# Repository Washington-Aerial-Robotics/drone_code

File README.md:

# drone_code
WAAR Drone Code Base

Under IMU_ESP32_test_stuff, visual_task.py allows for attutide visualization, either using live data while connected to the ESP32, or simulating stored data. The box represents the imu itself, and the red line is the accel data.

To run visual_task.py using simulated data, just ensure you have the python packages under requirements.txt, and enter "S" when prompted.

To run visual_task.py using live data, first connect to the esp32 and update PORT under visual_task.py and platformio.ini. Ensure all packages under requirements.txt are installed, then simply run visual_task.py and enter "C" when prompted.

TODO:

In general, start making objects instead of making big scripts.

Ensure proper madgewick filtering. Change visualization to use quaternions from madgewick filter. Optimize refresh rates. Add option to print out script suitable for the magneto calibration tool.

Design simple kalman filter for position. Create alternate visualizer which tracks position as well as attiude. Consider adding offset parameters for how far the imu is away from the cg of the drone.

Object for visualization, simple rotations, and for general positioning, both using quaternions.

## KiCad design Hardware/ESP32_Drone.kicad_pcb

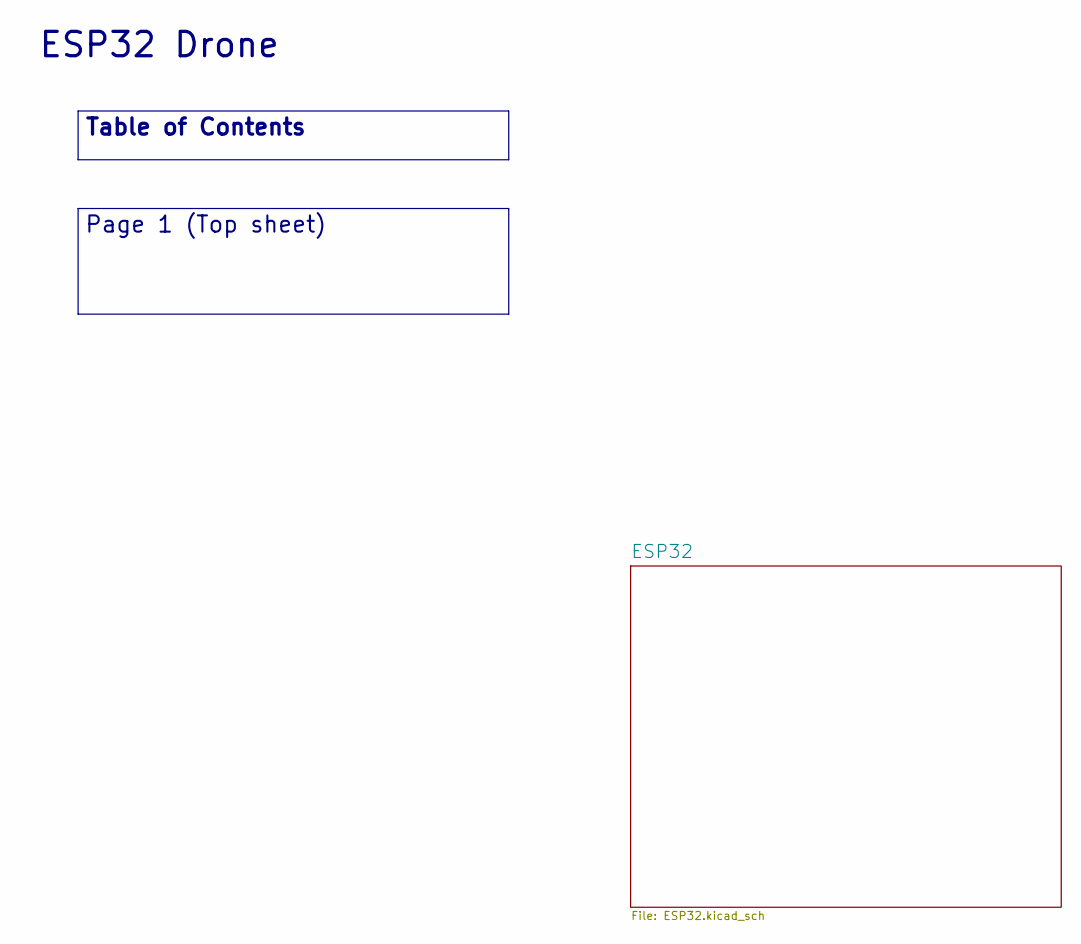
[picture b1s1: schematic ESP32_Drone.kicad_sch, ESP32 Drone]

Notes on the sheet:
ESP32 Drone
Table of Contents
Page 1 (Top sheet)

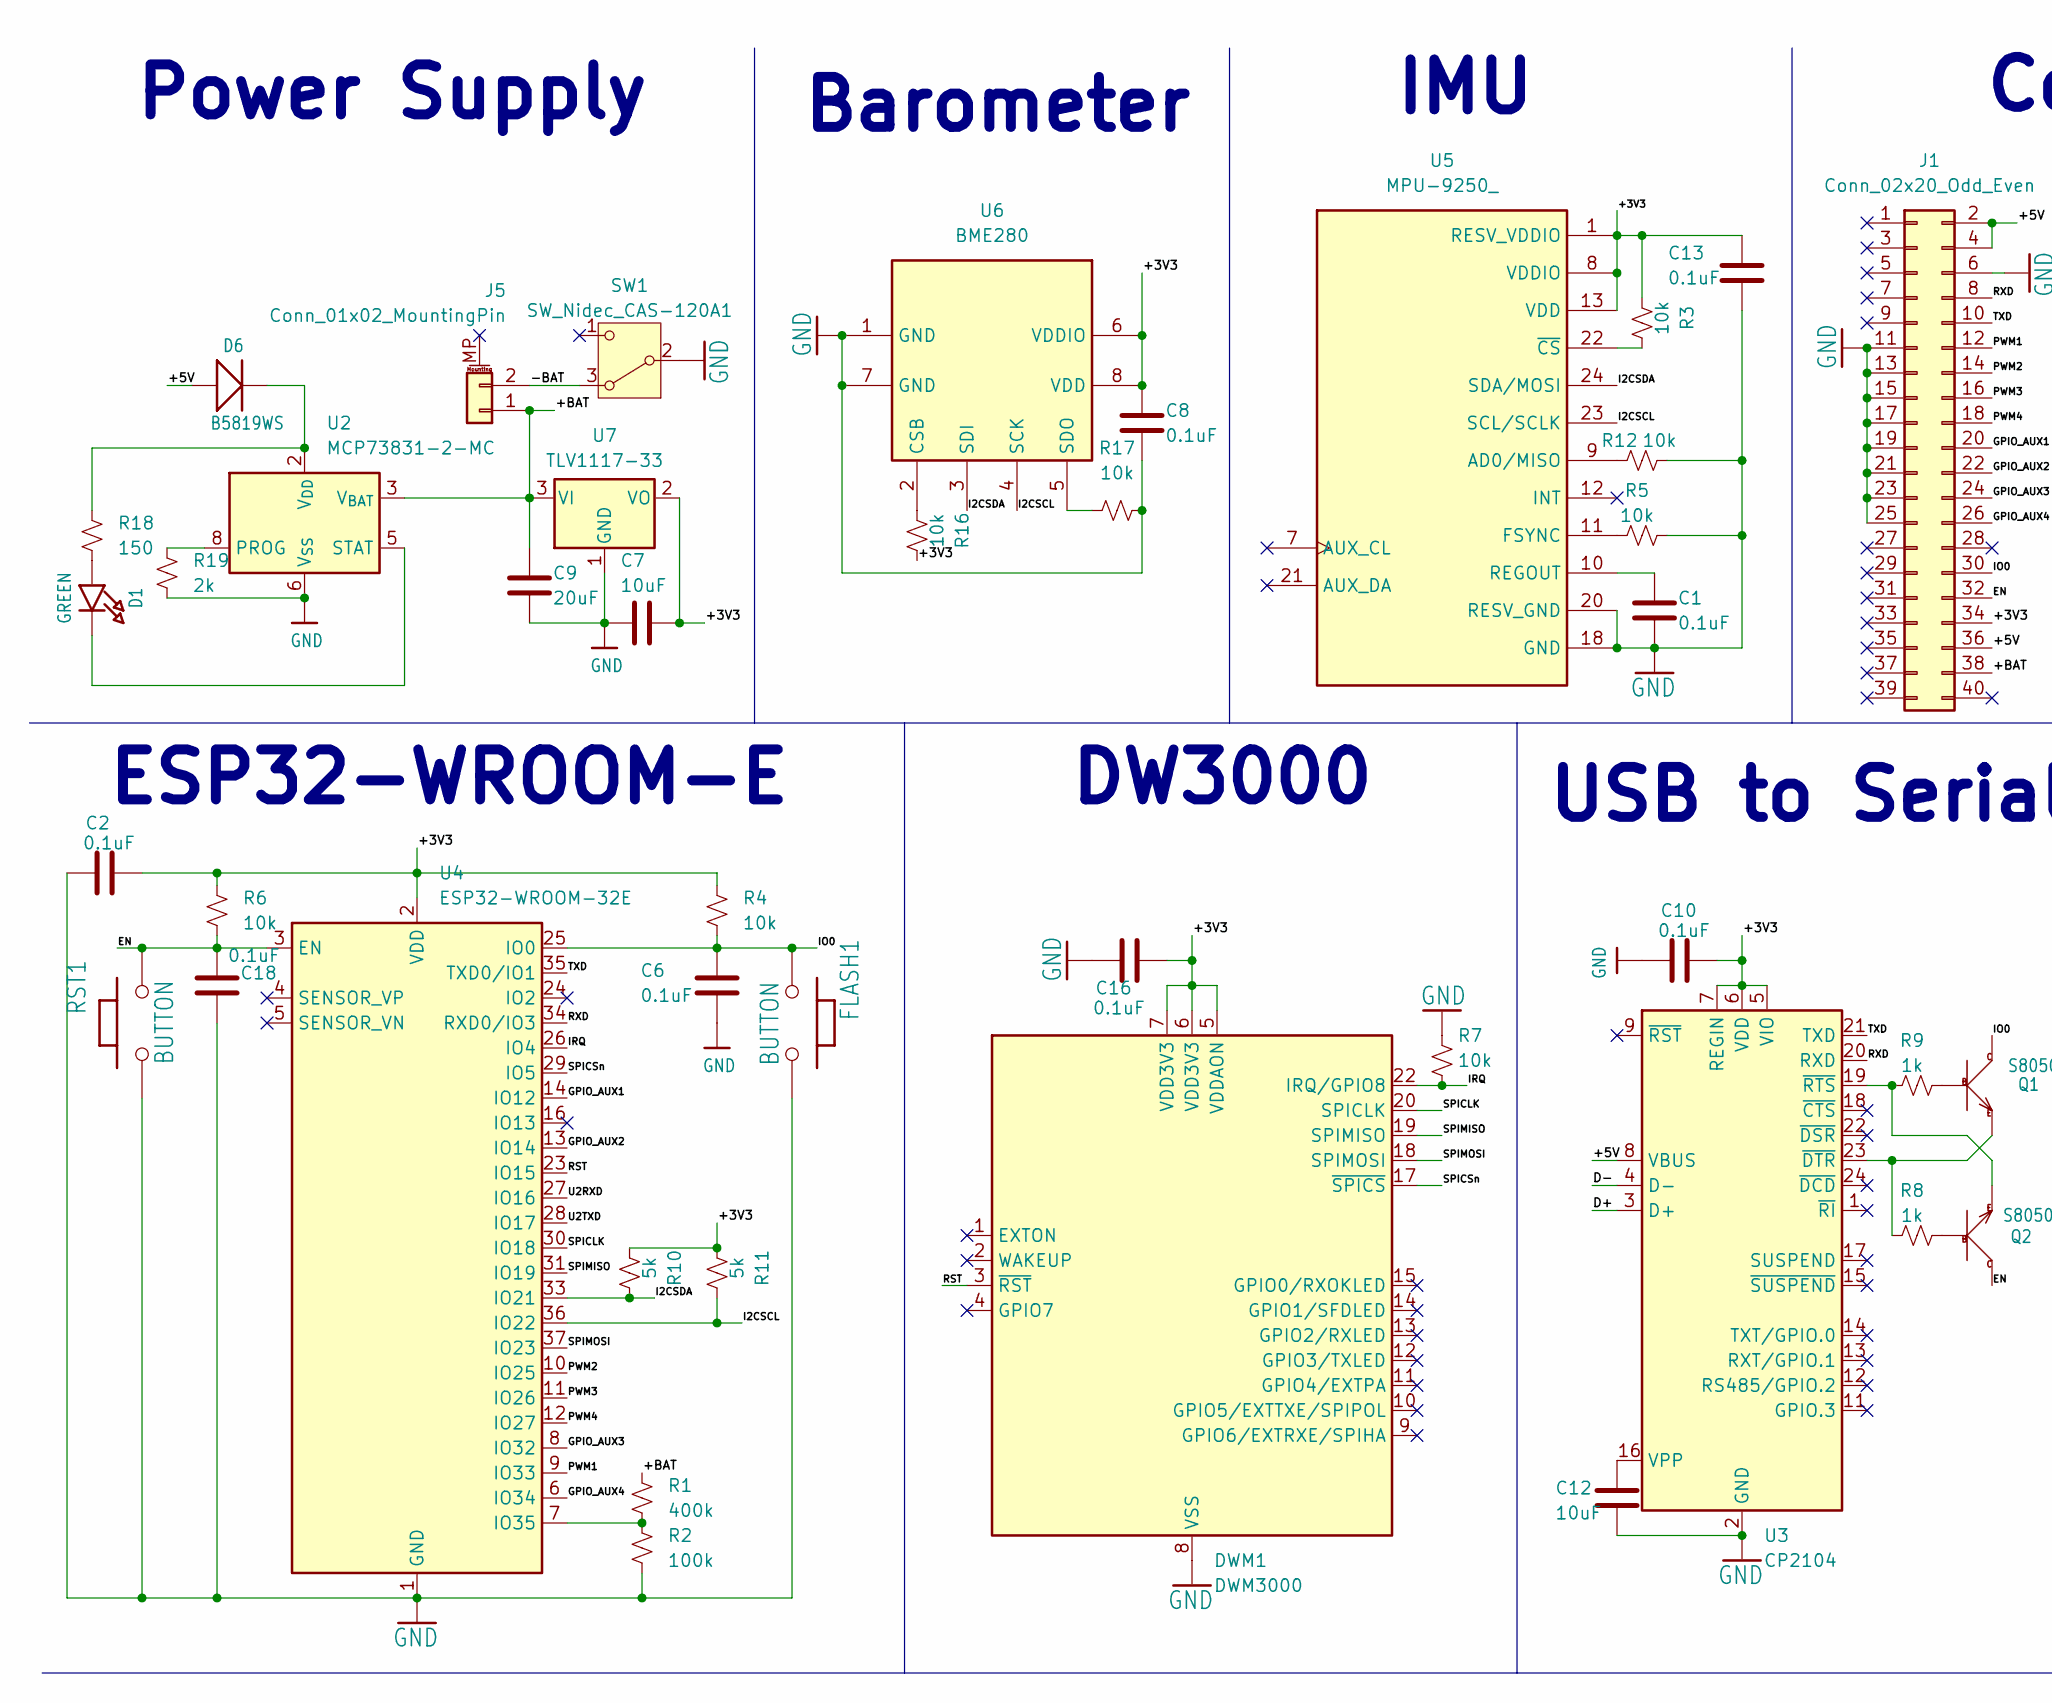
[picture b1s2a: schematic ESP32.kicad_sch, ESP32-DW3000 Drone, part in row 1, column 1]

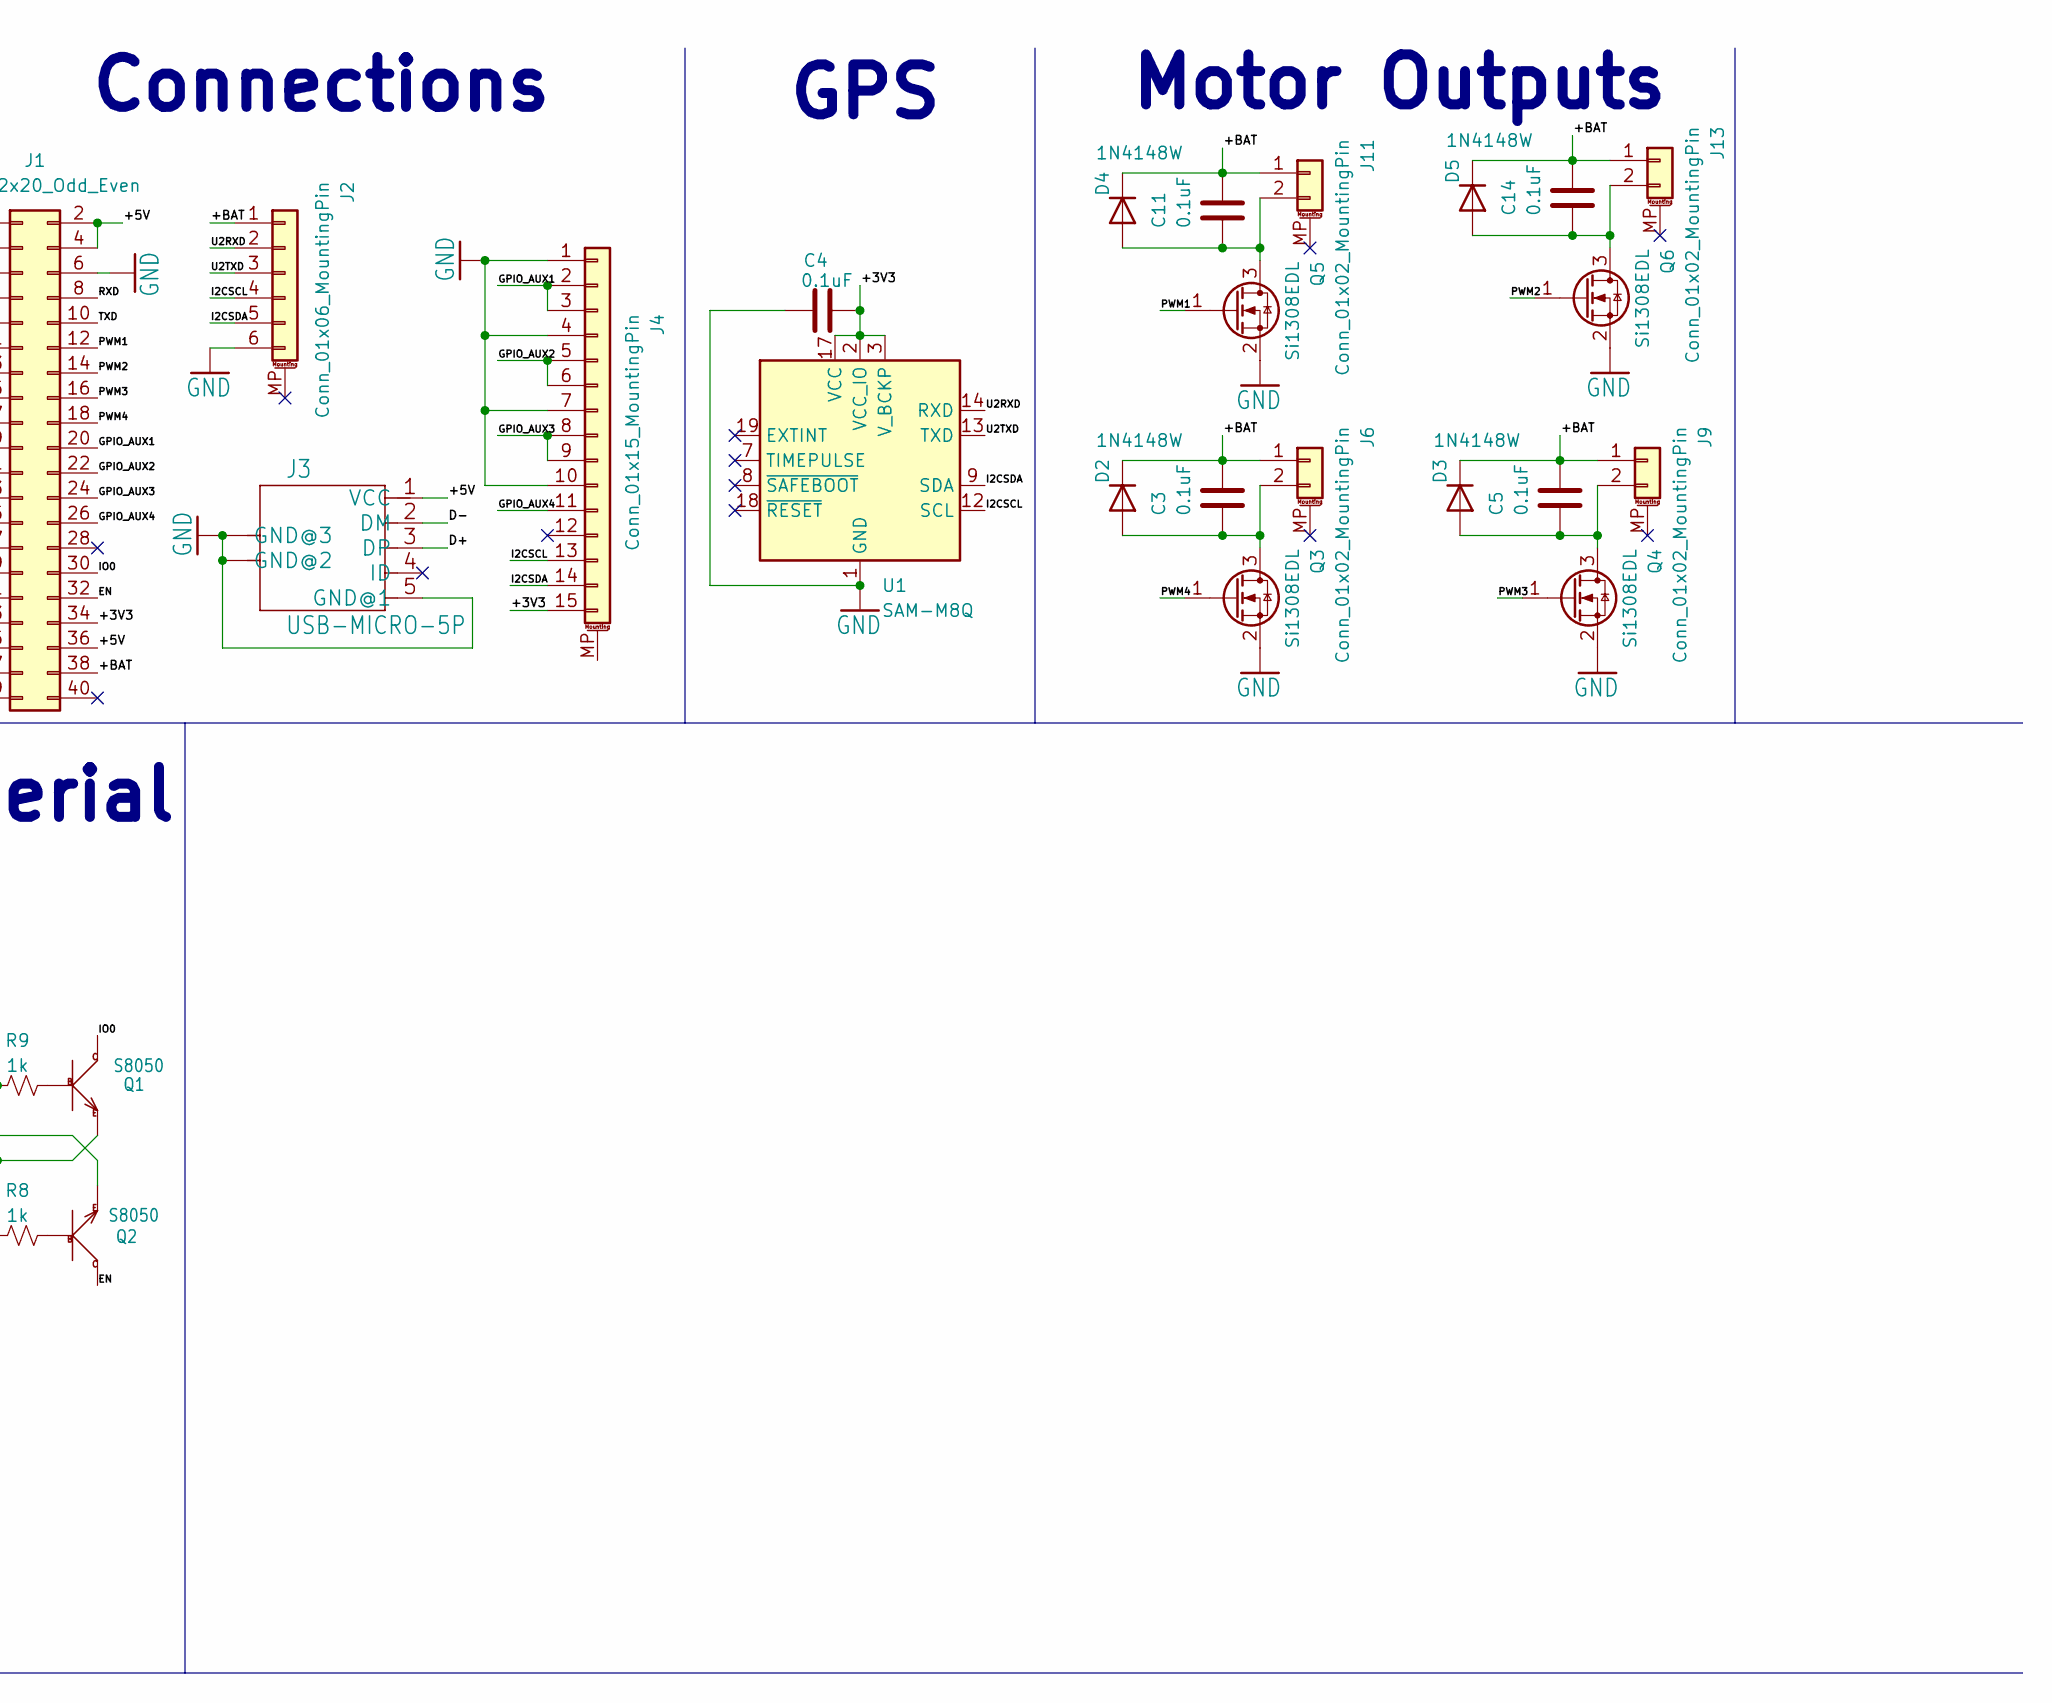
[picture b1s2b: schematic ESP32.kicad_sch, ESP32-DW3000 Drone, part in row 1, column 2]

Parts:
C1, C2, C3, C4, C5, C6, C8, C10, C11, C13, C14, C16, C18: 0.1uF; C_0603_1608Metric_Pad1.08x0.95mm_HandSolder
C7, C12: 10uF; C_0603_1608Metric_Pad1.08x0.95mm_HandSolder
C9: 20uF; C_0603_1608Metric_Pad1.08x0.95mm_HandSolder
D1: GREEN; CHIPLED_0805_NOOUTLINE
D2, D3, D4, D5: 1N4148W; D_SOD-123
D6: B5819WS; SOD323
DWM1: DWM3000; DWM1000
FLASH1: BUTTON; 157SW
J1: Conn_02x20_Odd_Even; PinHeader_2x20_P2.54mm_Vertical
J2: Conn_01x06_MountingPin; JST_GH_BM06B-GHS-TBT_1x06-1MP_P1.25mm_Vertical
J3: USB-MICRO-5P; MICRO-USB-5P
J4: Conn_01x15_MountingPin; TE_1-84952-5_1x15-1MP_P1.0mm_Horizontal
J5: Conn_01x02_MountingPin; JST_PH_S2B-PH-SM4-TB_1x02-1MP_P2.00mm_Horizontal
J6, J9, J11, J13: Conn_01x02_MountingPin; JST_GH_BM02B-GHS-TBT_1x02-1MP_P1.25mm_Vertical
Q1, Q2: S8050; SOT23
Q3, Q4, Q5, Q6: Si1308EDL; SOT-323_SC-70
R1: 400k; R_0603_1608Metric_Pad0.98x0.95mm_HandSolder
R2: 100k; R_0603_1608Metric_Pad0.98x0.95mm_HandSolder
R3, R4, R5, R6, R7, R12, R16, R17: 10k; R_0603_1608Metric_Pad0.98x0.95mm_HandSolder
R8, R9: 1k; R_0603_1608Metric_Pad0.98x0.95mm_HandSolder
R10, R11: 5k; R_0603_1608Metric_Pad0.98x0.95mm_HandSolder
R18: 150; R_0603_1608Metric_Pad0.98x0.95mm_HandSolder
R19: 2k; R_0603_1608Metric_Pad0.98x0.95mm_HandSolder
RST1: BUTTON; 157SW
SW1: SW_Nidec_CAS-120A1; Nidec_Copal_CAS-120A
U1: SAM-M8Q; ublox_SAM-M8Q
U2: MCP73831-2-MC; DFN-8-1EP_3x2mm_P0.5mm_EP1.7x1.4mm
U3: CP2104; QFN-24-1EP_4x4mm_P0.5mm_EP2.6x2.6mm
U4: ESP32-WROOM-32E; ESP32-WROOM-32D
U5: MPU-9250_; InvenSense_QFN-24_3x3mm_P0.4mm
U6: BME280; Bosch_LGA-8_2.5x2.5mm_P0.65mm_ClockwisePinNumbering
U7: TLV1117-33; SOT-223-3_TabPin2

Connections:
/ESP32/+3V3: C2.2, C4.2, C7.2, C8.1, C10.2, C13.1, C16.2, DWM1.5 (VDDAON), DWM1.6 (VDD3V3), DWM1.7 (VDD3V3), J1.34, J4.15, R3.2, R4.1, R6.1, R10.2, R11.2, R16.1, U1.2 (VCC_IO), U1.3 (V_BCKP), U1.17 (VCC), U3.5 (VIO), U3.6 (VDD), U3.7 (REGIN), U4.2 (VDD), U5.1 (RESV_VDDIO), U5.8 (VDDIO), U5.13 (VDD), U6.6 (VDDIO), U6.8 (VDD), U7.2 (VO)
/ESP32/+5V: D6.+, J1.2, J1.4, J1.36, J3.1 (VCC), U3.8 (VBUS)
/ESP32/+BAT: C3.1, C5.1, C9.1, C11.1, C14.1, D2.1 (K), D3.1 (K), D4.1 (K), D5.1 (K), J1.38, J2.1, J5.1, J6.1, J9.1, J11.1, J13.1, R1.1, U2.3 (V_{BAT}), U2.4 (V_{BAT}), U7.3 (VI)
/ESP32/-BAT: J5.2, SW1.3 (A)
/ESP32/D+: J3.3 (DP), U3.3 (D+)
/ESP32/D-: J3.2 (DM), U3.4 (D-)
/ESP32/EN: C18.1, J1.32, Q2.3 (C), R6.2, RST1.2, U4.3 (EN)
/ESP32/GPIO_AUX1: J1.20, J4.2, J4.3, U4.14 (IO12)
/ESP32/GPIO_AUX2: J1.22, J4.5, J4.6, U4.13 (IO14)
/ESP32/GPIO_AUX3: J1.24, J4.8, J4.9, U4.8 (IO32)
/ESP32/GPIO_AUX4: J1.26, J4.11, U4.6 (IO34)
/ESP32/I2CSCL: J2.4, J4.13, R11.1, U1.12 (SCL), U4.36 (IO22), U5.23 (SCL/SCLK), U6.4 (SCK)
/ESP32/I2CSDA: J2.5, J4.14, R10.1, U1.9 (SDA), U4.33 (IO21), U5.24 (SDA/MOSI), U6.3 (SDI)
/ESP32/IO0: C6.1, FLASH1.1, J1.30, Q1.3 (C), R4.2, U4.25 (IO0)
/ESP32/IRQ: DWM1.22 (IRQ/GPIO8), R7.2, U4.26 (IO4)
/ESP32/PWM1: J1.12, Q5.1 (G), U4.9 (IO33)
/ESP32/PWM2: J1.14, Q6.1 (G), U4.10 (IO25)
/ESP32/PWM3: J1.16, Q4.1 (G), U4.11 (IO26)
/ESP32/PWM4: J1.18, Q3.1 (G), U4.12 (IO27)
/ESP32/RST: DWM1.3 (~RST), U4.23 (IO15)
/ESP32/RXD: J1.8, U3.20 (RXD), U4.34 (RXD0/IO3)
/ESP32/SPICLK: DWM1.20 (SPICLK), U4.30 (IO18)
/ESP32/SPICSn: DWM1.17 (~SPICS), U4.29 (IO5)
/ESP32/SPIMISO: DWM1.19 (SPIMISO), U4.31 (IO19)
/ESP32/SPIMOSI: DWM1.18 (SPIMOSI), U4.37 (IO23)
/ESP32/TXD: J1.10, U3.21 (TXD), U4.35 (TXD0/IO1)
/ESP32/U2RXD: J2.2, U1.14 (RXD), U4.27 (IO16)
/ESP32/U2TXD: J2.3, U1.13 (TXD), U4.28 (IO17)
GND: C1.2, C2.1, C4.1, C6.2, C7.1, C8.2, C9.2, C10.1, C12.2, C13.2, C16.1, C18.2, DWM1.8 (VSS), DWM1.16 (VSS), DWM1.21 (VSS), DWM1.23 (VSS), DWM1.24 (VSS), FLASH1.2, J1.6, J1.11, J1.13, J1.15, J1.17, J1.19, J1.21, J1.23, J1.25, J2.6, J3.5 (GND@1), J3.E1 (GND@3), J3.E2 (GND@2), J3.P1 (GND@3), J3.P2 (GND@2), J4.1, J4.4, J4.7, J4.10, Q3.2 (S), Q4.2 (S), Q5.2 (S), Q6.2 (S), R2.2, R5.1, R7.1, R12.1, R17.2, R19.2, RST1.1, SW1.2 (B), U1.1 (GND), U1.4 (GND), U1.5 (GND), U1.6 (GND), U1.10 (GND), U1.11 (GND), U1.15 (GND), U1.16 (GND), U1.20 (GND), U2.6 (V_{SS}), U3.2 (GND), U3.25 (GND), U4.1 (GND), U4.15 (GND), U4.38 (GND), U4.39 (GND), U5.18 (GND), U5.20 (RESV_GND), U6.1 (GND), U6.7 (GND), U7.1 (GND)
unnamed: D1.A, R18.2
unnamed: C3.2, D2.2 (A), J6.2, Q3.3 (D)
unnamed: C5.2, D3.2 (A), J9.2, Q4.3 (D)
unnamed: C11.2, D4.2 (A), J11.2, Q5.3 (D)
unnamed: C14.2, D5.2 (A), J13.2, Q6.3 (D)
unnamed: D6.-, R18.1, U2.1 (V_{DD}), U2.2 (V_{DD})
unnamed: Q1.1 (B), R9.1
unnamed: Q1.2 (E), R8.2, U3.23 (~DTR)
unnamed: Q2.1 (B), R8.1
unnamed: Q2.2 (E), R9.2, U3.19 (~RTS)
unnamed: R19.1, U2.8 (PROG)
unnamed: D1.C, U2.5 (STAT)
unnamed: C12.1, U3.16 (VPP)
unnamed: R1.2, R2.1, U4.7 (IO35)
unnamed: R12.2, U5.9 (AD0/MISO)
unnamed: R5.2, U5.11 (FSYNC)
unnamed: C1.1, U5.10 (REGOUT)
unnamed: R3.1, U5.22 (~CS)
unnamed: R16.2, U6.2 (CSB)
unnamed: R17.1, U6.5 (SDO)

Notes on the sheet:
IMU
Barometer
GPS
Connections
DW3000
Motor Outputs
USB to Serial
ESP32-WROOM-E
Power Supply

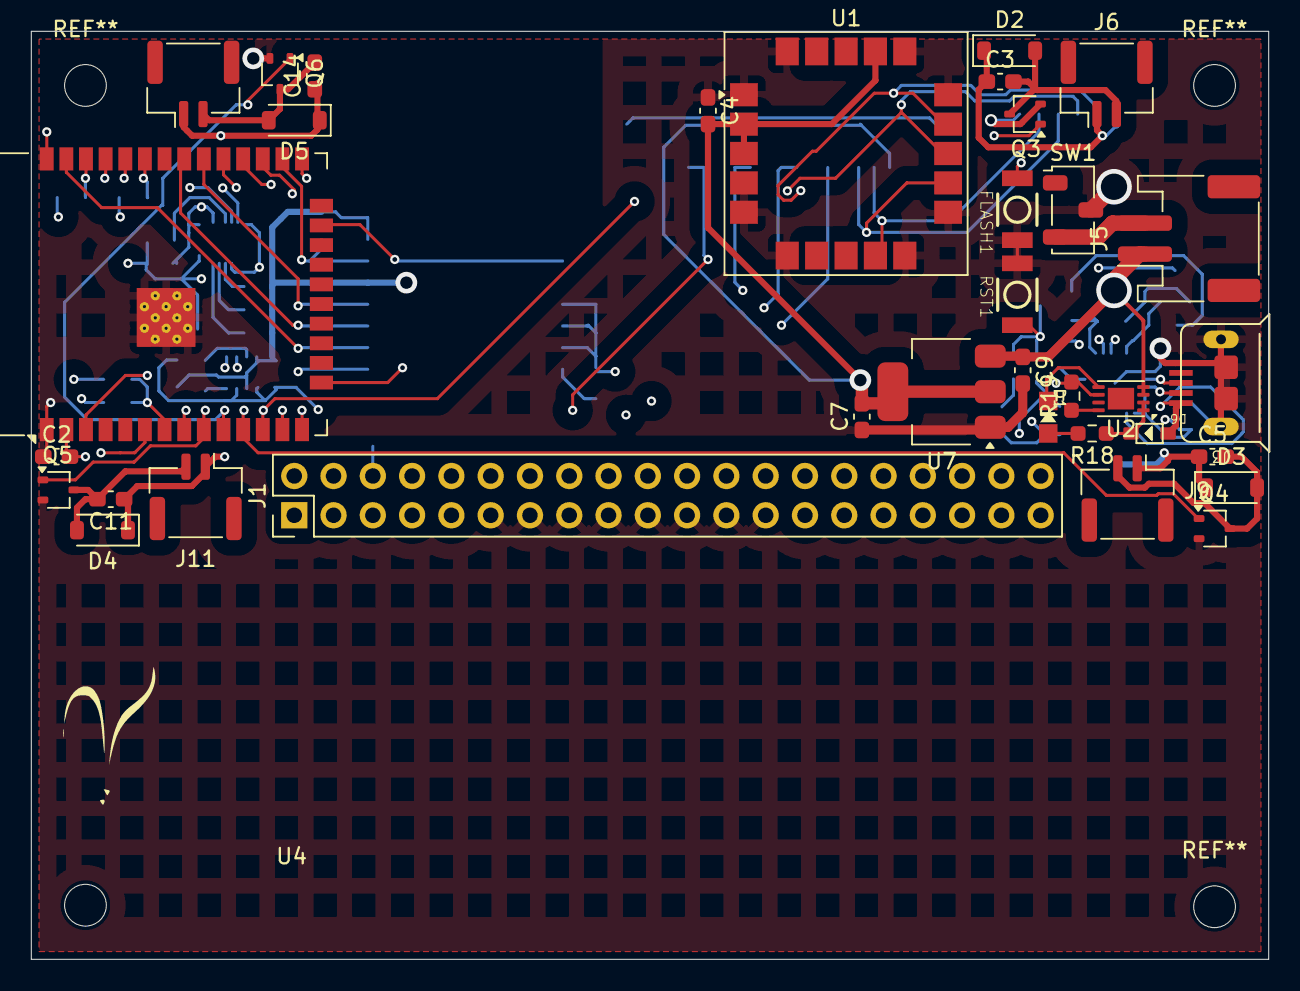
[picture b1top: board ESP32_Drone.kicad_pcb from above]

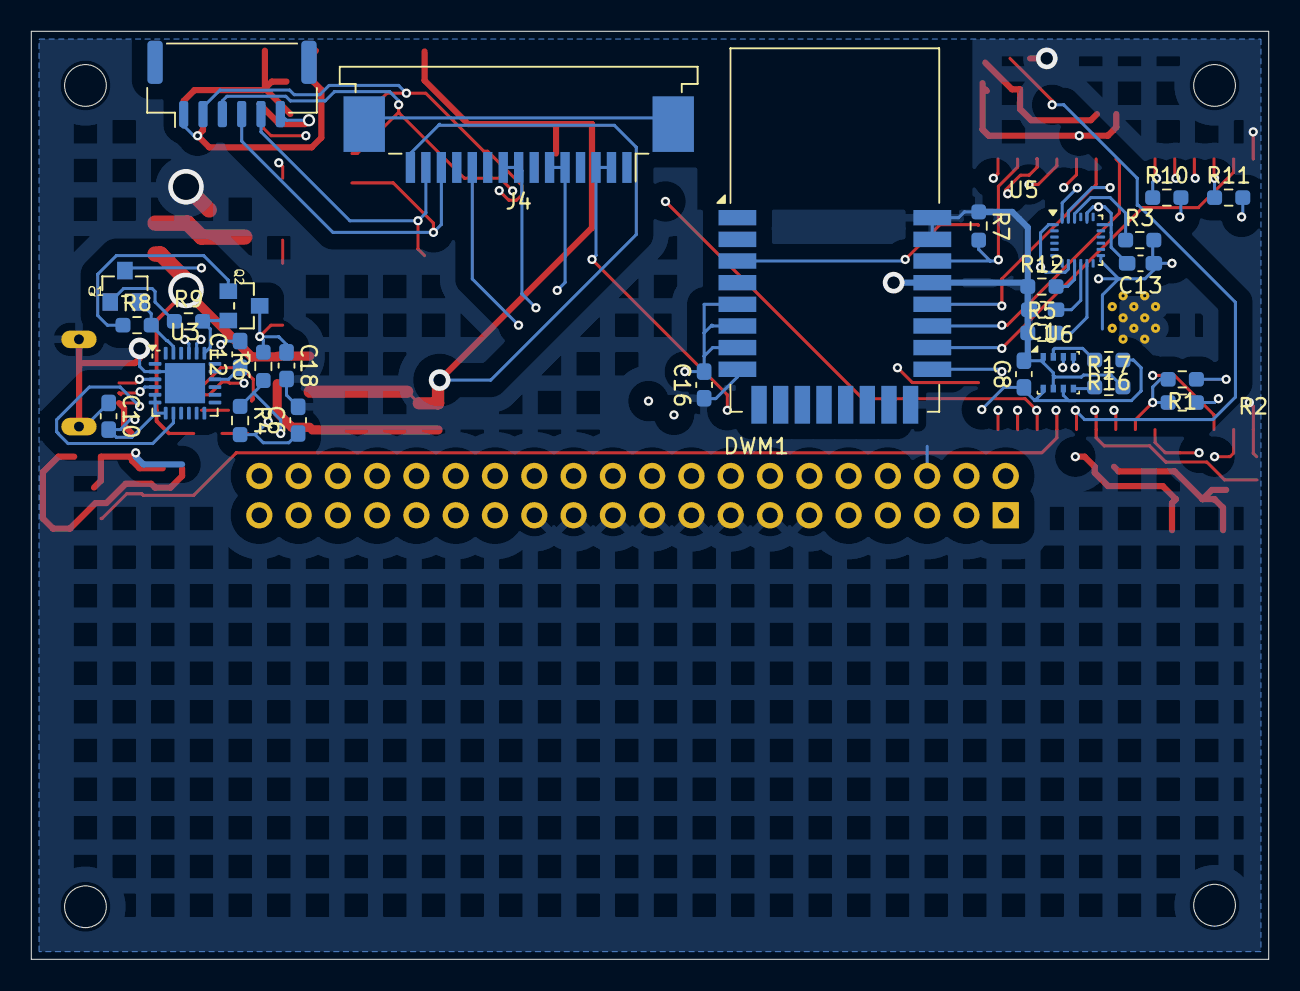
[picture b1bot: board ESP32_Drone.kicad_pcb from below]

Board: 4 copper layers, 80.0 x 60.0 mm, 64 parts (30 on the bottom side), 49 nets.

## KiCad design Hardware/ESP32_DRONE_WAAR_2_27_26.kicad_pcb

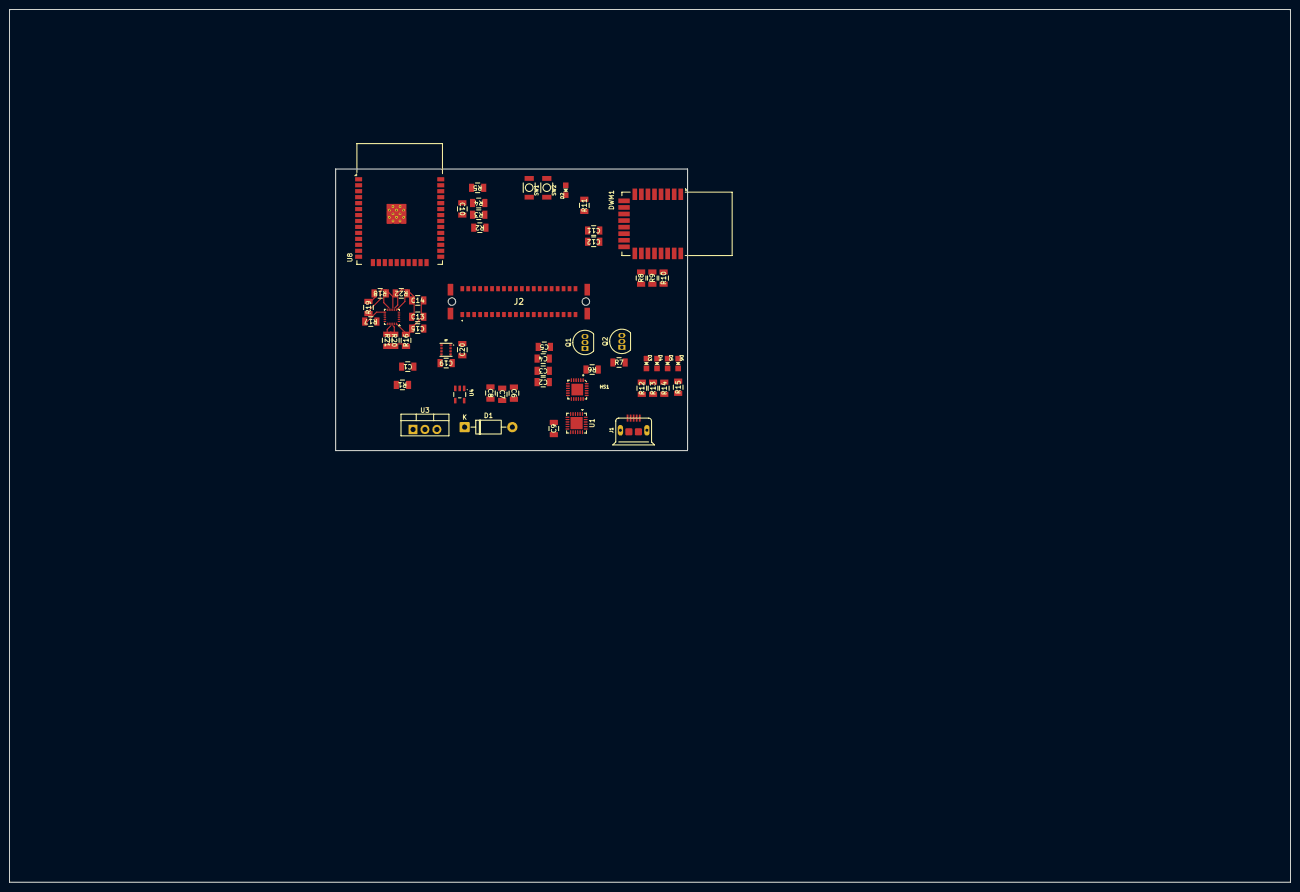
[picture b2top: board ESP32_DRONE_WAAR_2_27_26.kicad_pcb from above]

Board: 2 copper layers, 273.0 x 186.0 mm, 59 parts (0 on the bottom side), 51 nets.

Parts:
C1, C2, C3, C4, C6, C8, C9, C11: 10µF; CAPC340180_88N_KEM-L
C5: 1.0µF; CAPC340180_88N_KEM-L
C7, C10: 100nF; CAPC340180_88N_KEM-L
C12: 0.1µF; CAPC340180_88N_KEM-L
C13: 0.01uf; CAPC340180_88N_KEM-L
C14: 0.1uf; CAPC340180_88N_KEM-L
C15: 0.1uF; CAPC340180_88N_KEM-L
C19: 0.1 uF; CAPC340180_88N_KEM-L
C20: 1 uF; CAPC340180_88N_KEM-L
D1: 1N4005; D_DO-41_SOD81_P10.16mm_Horizontal
D2, D3, D4, D5, D6: LED; CHIPLED_0805_NOOUTLINE
DWM1: DWM3000; DWM1000
HS1: Heatsink_Pad; QFN24_4MM_SMSC
J1: USB_B_Micro; MICRO-USB-5P
J2: Conn_02x20_Odd_Even_MountingPin; 204632E
Q1, Q2: S8050; TO-92_Inline
R1, R4, R5, R11, R16, R17, R18, R19, R20, R21, R22: 10k; CAPC340180_88N_KEM-L
R2, R3: 470; CAPC340180_88N_KEM-L
R6, R7, R8, R9, R10: 1k; CAPC340180_88N_KEM-L
R12, R13, R14, R15: 470R; CAPC340180_88N_KEM-L
SW1, SW2: SW_MEC_5G; 157SW
U1: CP2104; QFN-24-1EP_4x4mm_P0.5mm_EP2.6x2.6mm
U3: LD1117V33; TO-220-3_Vertical
U4: ME6217C33M5G; SOT23-5
U5: MPU-9250; InvenSense_QFN-24_3x3mm_P0.4mm
U7: BME280; PSON65P250X250X100-8N
U8: ESP32-WROOM-32

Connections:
+5V: J2.2, J2.4, J2.36
/<NO NET>: DWM1.19 (SPIMISO), U8.31 (IO19)
/CLOCK: R1.2, U4.3 (CE)
/DTR: Q1.1 (E), R7.1, U1.23 (~DTR)
/IO0: J2.30, Q1.3 (C), R2.1, R5.2
/IO4: DWM1.17 (~SPICS), U8.26 (IO4)
/IO18: DWM1.20 (SPICLK), U8.30 (IO18)
/IO23: DWM1.18 (SPIMOSI), U8.37 (IO23)
/IO27: R10.2, U8.12 (IO27)
/IO32: R9.1, U8.8 (IO32)
/IO33: R8.1, U8.9 (IO33)
/IO34: DWM1.22 (IRQ/GPIO8), R11.1
/LEDRX: DWM1.13 (GPIO2/RXLED), R13.1
/LEDRXOK: DWM1.15 (GPIO0/RXOKLED), R15.1
/LEDSFD: DWM1.14 (GPIO1/SFDLED), R14.1
/LEDTX: DWM1.12 (GPIO3/TXLED), R12.1
/PWM1: J2.12, U8.14 (IO12)
/PWM2: J2.14, U8.16 (IO13)
/PWM3: J2.16, U8.13 (IO14)
/PWM4: J2.18, U8.23 (IO15)
/RESET: Q2.3 (C), U8.3 (EN)
/RTS: Q2.1 (E), R6.1, U1.19 (~RTS)
/RXD: J2.8, U1.20 (RXD)
/TXD: J2.10, U1.21 (TXD)
/VBUS: C4.1, C6.1, C7.1, D1.2 (A), J1.1 (VBUS), R1.1, U1.8 (VBUS), U4.1 (Vin)
/VDDV5: C2.1, D1.1 (K), U3.3 (VI)
GND: C1.1, C2.2, C3.2, C4.2, C5.2, C6.2, C7.2, C8.2, C9.2, C10.2, C11.2, C12.1, C13.2, C14.2, C15.2, C19.2, C20.2, D3.1 (K), D4.1 (K), D5.1 (K), D6.1 (K), DWM1.8 (VSS), DWM1.16 (VSS), DWM1.21 (VSS), DWM1.23 (VSS), DWM1.24 (VSS), HS1.1, J1.5 (GND), J2.6, J2.11, J2.13, J2.15, J2.17, J2.19, J2.21, J2.23, J2.25, R3.2, R11.2, R18.2, R19.2, SW1.1 (A), SW1.2 (A), SW2.1 (A), SW2.2 (A), U1.2 (GND), U1.25 (GND), U3.1 (GND), U4.2 (Vss), U5.18 (GND), U5.20 (RESV_GND), U7.1 (GND), U7.7 (GND), U8.1 (GND), U8.15 (GND), U8.38 (GND), U8.39 (GND)
unnamed: C10.1, R4.2
unnamed: D2.1 (K), R3.1
unnamed: D3.2 (A), R12.2
unnamed: D4.2 (A), R13.2
unnamed: D5.2 (A), R14.2
unnamed: D6.2 (A), R15.2
unnamed: DWM1.1 (EXTON), R8.2
unnamed: DWM1.2 (WAKEUP), R9.2
unnamed: DWM1.3 (~RST), R10.1
unnamed: J1.3 (D+), U1.3 (D+)
unnamed: J1.2 (D-), U1.4 (D-)
unnamed: Q1.2 (B), R6.2
unnamed: Q2.2 (B), R7.2
unnamed: C9.1, U1.16 (VPP)
unnamed: C3.1, U3.2 (VO)
unnamed: R19.1, U5.9 (AD0/MISO)
unnamed: R22.1, U5.7 (AUX_CL)
unnamed: R21.1, U5.21 (AUX_DA)
unnamed: R18.1, U5.11 (FSYNC)
unnamed: C15.1, U5.10 (REGOUT)
unnamed: R20.1, U5.22 (~CS)
SCL_BME: C1.2, C5.1, C8.1, C11.1, C12.2, C13.1, C14.1, C19.1, C20.1, D2.2 (A), DWM1.5 (VDDAON), DWM1.6 (VDD3V3), DWM1.7 (VDD3V3), J2.34, R4.1, R5.1, R16.1, R17.2, R20.2, R21.2, R22.2, U1.5 (VIO), U1.6 (VDD), U1.7 (REGIN), U4.5 (Vout), U5.1 (RESV_VDDIO), U5.8 (VDDIO), U5.13 (VDD), U7.2 (CSB), U7.3 (SDI), U7.4 (SCK), U7.6 (VDDIO), U7.8 (VDD), U8.2 (VDD), U8.27 (IO16), U8.28 (IO17)
SCL_IMU: R17.1, U5.23 (SCL/SCLK), U8.36 (IO22)
SDA_IMU: R16.2, U5.24 (SDA/MOSI), U8.33 (IO21)

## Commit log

2025-07-28 message
2025-10-13 Inital upload
2025-10-13 Initial upload
2025-11-11 Add files via upload
    Initial commit of PCB schematic
2025-11-13 Initial Release - ESP32 FC
2025-11-13 Version 2 11/13 15:26
2025-11-16 Create a
2025-11-17 v2 11/16/25 18:27
2025-11-17 v2 11/16/25 18:28
    Almost fully complete schematic. Issue: ESP32-WROVER module is different than reference, so its implementation is incomplete. No Footprints assigned. Requires hardware lead review to chose correct ES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
2025-11-19 Added esp32 connection ui
2025-11-19 esp32 ui code added
2025-12-13 Add files via upload
    Added calibrated sensor
2025-12-13 Delete DataCalibration directory
    Replacing with simpler python version
2025-12-13 Add files via upload
    Simpler flash and visualization process
2025-12-13 Update README with IMU testing instructions
    Added IMU_ESP32_test_stuff for real-time IMU attitude visualization.
2025-12-14 Mag calibration updates and environment setup
2025-12-16 Added simulator
2025-12-16 Update README.md
    Added direction for how to use simulator
2025-12-17 KiCad Files
2025-12-18 Create tests directory for drone functionality
    Add a tests directory for sensor calibration and simulations.
2025-12-18 Add script to plot calibrated and uncalibrated magnetometer data
    This script reads raw magnetometer data, applies calibration using defined parameters, and visualizes both raw and calibrated measurements in 2D and 3D plots.
2025-12-21 Preliminary test version
2025-12-31 Communication with forwarding capabilities
2026-01-10 added kalmanfilter.h
2026-01-10 Added kalmanFilter.h, which handles the actual NED state
2026-01-21 Create PERIPHERALS
2026-01-24 carrier board model
    still need to add holes and risers
2026-01-25 Rename Hardware/CAD/PERIPHERALS/carrierboard.SLDPRT to Hardware/CAD/PERIPHERALS/CARRIERBOARD/carrierboard_v1.SLDPRT
2026-01-25 completed model
2026-01-25 Rename carrierboard.SLDPRT to carrierboardv2.SLDPRT
2026-01-25 Rename carrierboardv2.SLDPRT to carrierboard_v2.SLDPRT
2026-02-04 import
2026-02-04 Add files via upload
    Version 1 iteration-does not include camera
2026-02-04 Add files via upload
    Version 1 assembly. Includes motor mounts, flight controller holder
2026-02-04 import
    technically for the cm4 but the dimensions are the same and the holes seem to be good
2026-02-10 up to date cad files properly sorted
2026-02-11 Move old files into a folder
2026-02-11 beginning edits
2026-02-11 propeller motor
2026-02-11 Add tinympc-python as submodule
2026-02-11 tracking submodule update
2026-02-18 Updated flight.h, flight.cpp, KalmanFilter3d.h
    Updated flight.h, flight.cpp, KalmanFilter3d.h
    Be warned, this code has not been debugged.
2026-02-18 Added newer versions of kaf_drone h and cpp
    Added newer versions of kaf_drone h and cpp, not necessarily final versions. Added quaternion to state vector, and changes Kent made
2026-02-24 Add files via upload
    This is the component that helps attach the DC to DC converter and the landing gear to the frame.
2026-02-25 up to date files
2026-02-25 up to date cad
2026-02-25 added colors and fixed assembly legs rotation
2026-02-25 all cad files and assembly up to date
2026-02-25 mpc: read data stream from kalman filter
2026-02-26 REAL NEW CAD
2026-02-26 propellers + extend frame a bit + add some swag (color)
2026-02-26 fixed diegos ass mates on the pcb bracket
2026-02-28 Add file for Mono Camera
2026-02-28 battery model updated + mount
2026-02-28 stp file for mono camera
2026-02-28 Add files via upload
    singular camera model
2026-02-28 camera mount
